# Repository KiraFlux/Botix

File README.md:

<div align="center">

# Botix

**Open‑source educational mobile robot project**

</div>

---

> **[Read this in Russian](README.ru.md)**

<br><br>

<div align="center">

## Overview

</div>

Designed for school robotics clubs, Olympiad preparation (All-Russian Olympiad, Moscow Olympiad, Russian Robotics Olympiad), and fast prototyping at hackathons. All parts are 3D‑printable, electronics are cheap and widely available.

- Two drive motors with encoders (JGA25 12V, 77-170 RPM).
- Optional [two‑degree‑of‑freedom manipulator](docs/gallery.md#2026_05_botix_esp32) (arm + gripper).
- Chassis prints in ~5 hours on a standard FDM printer; flat parts, tongue‑and‑groove assembly with screws.

<br><br>

<div align="center">

## Variants

<table>

<tr>
<td colspan="2" align="center">

**Basic**

</td>
<td colspan="2" align="center">

**Advanced**

</td>
</tr>

<tr>
<td style="padding: 0;"></td>
<td style="padding: 0;"></td>
<td style="padding: 0;"></td>
<td style="padding: 0;"></td>
</tr>

<tr valign="top">
<td colspan="2">

**For:** 
- Olympiad practice (VSOSH, MOSH, RRO), learning programming, control algorithms

**Features:**
- Arduino UNO + any motor shield
- Classic competition‑ready setup
- Simple, reliable, well‑documented

</td>
<td colspan="2">

**For:** 
- Complex algorithms, research, hackathons

**Features:**
- ESP32 as main controller (works standalone like Basic)
- Optional **[botix-esp32 firmware](botix-esp32/)** adds:
  - Remote control & telemetry via WiFi or ESP‑NOW
  - Integration with MAVLink (QGC, ROS) or custom raw protocol
  - Persistent configuration & CLI for debugging
  - LIDAR & encoder support

</td>
</tr>

<tr>
<td colspan="2" align="center">

[more_photos](docs/gallery.md#2026_07_botix_uno), 
[assembly_guide](docs/assembly_guide.md)

</td>
<td colspan="2" align="center">

[more_photos](docs/gallery.md#2026_07_botix_esp32), 
[assembly_guide](docs/assembly_guide.md), 
[firmware_docs](botix-esp32/README.md)

</td>
</tr>

</table>

</div>

> View the [printable parts catalog](docs/catalog.md).

<br><br>

<div align="center">

## Hardware

</div>

### Electronics

- **Controller** - any Developing board (Arduino UNO, ESP32, etc.). See the [assembly guide](docs/assembly_guide.md) for specific models and wiring.
- **Power board** - custom design, powered by 3×14500 cells (3S). Three independent regulators: 2 × Mini560 Pro (5V), 1 × LM2596S module (adjustable). Variants:
  - [PCB manufacturing](docs/gallery.md#2026_07_botix_power_v2_pcb_order) - production order
  - [DIY toner transfer (double-sided)](docs/gallery.md#2026_07_botix_power_v2_ttm_double)
  - [DIY toner transfer (single-sided)](docs/gallery.md#2026_07_botix_power_v2_ttm_single)

See [`ecad/README.md`](ecad/README.md).

### Mechanics

- All 3D models are in [`mcad/`](mcad/).
- [One Main assembly](mcad/botix.fcstd).
- [Chassis](mcad/chassis/) and [attachments](mcad/attachments).

See [`mcad/README.md`](mcad/README.md).

### External models

- Live in [`cadref/`](cadref/).
- Models of purchased components used as references to check fit.

See [`cadref/README.md`](cadref/README.md).

> For visual references of different robot configurations and hardware revisions, see the [project gallery](docs/gallery.md).

<br><br>

<div align="center">

## Software

<table>

<tr>
<td align="center">

**botix-esp32 firmware**

</td>
<td align="center">

**pybotix – host Python API (coming soon)**

</td>
</tr>

<tr valign="top">
<td>

The **[modular firmware](botix-esp32/)** for the Advanced variant is written in C++20 and built with PlatformIO. It provides:

- Interactive CLI for configuration and debugging
- MAVLink and RAW protocols
- ESP‑NOW and WiFi UDP transports
- Persistent configuration in NVS
- Units for motors, servos, encoders, and LIDAR

</td>
<td>

`pybotix` will be a Python package for the **host computer** (PC, Raspberry Pi). It will provide:

- Simple and safe robot control from Python
- Swarm support
- High‑level primitives for navigation and behaviors
- Eventually, block‑based code generation for education

</td>
</tr>

<tr>
<td align="center">

[firmware_docs](botix-esp32/README.md)

</td>
<td align="center">

</td>
</tr>

</table>

</div>

> `pybotix` runs on the host, not on the robot. It communicates with the robot via MAVLink or RAW protocols over WiFi/ESP‑NOW.

<br><br>

<div align="center">

## Who Is This For?

</div>

- **School students** - prepare for practical rounds of robotics Olympiads (VSOSH, MOSH, RRO). The Arduino‑based option fully matches competition regulations.
- **University students** - learn mobile robotics, navigation algorithms.
- **Hackathon participants** - the ESP32 variant with firmware provides a ready‑made infrastructure so you can focus on high‑level logic.
- **Teachers** - quickly set up robotics clubs on a low budget.

<br><br>

<div align="center">

## Quick Start

</div>

1. Read the [assembly guide](docs/assembly_guide.md).
2. Print parts from [`mcad/`](mcad/). Printable STEP files are attached to the [releases](../../releases).
3. Refer to schematics in [`ecad/`](ecad/) to assemble the electronics.
4. - For Basic: write and upload your own Arduino sketch using the motor shield library.
   - For Advanced: go to [`botix-esp32/`](botix-esp32/) and follow the firmware guide.

Before you start, make sure you have the following software installed:

| Purpose           | Software   | Version |
| ----------------- | ---------- | ------- |
| CAD (mechanics)   | FreeCAD    | 1.1.x   |
| CAD (electronics) | KiCad      | 10.x.x  |
| Slicer            | OrcaSlicer | 2.4.x   |
| Firmware build    | PlatformIO | 6.1.20  |
| Scripts runtime   | Python     | 3.14.x  |
| Render engine     | POV-Ray    | 3.7.x   |

> All tools are free and open‑source.

<br><br>

<div align="center">

## Contributing

Found a bug? Have an idea? Open an Issue or submit a Pull Request.  

</div>

> See [`CONTRIBUTING.md`](CONTRIBUTING.md) for guidelines.

<br><br>

<div align="center">

## Repository Structure & Licensing

| Path           | Description                                   |
| :------------- | :-------------------------------------------- |
| `docs/`        | Project documentation.                        |
| `cadref/`      | Reference CAD models of purchased components. |
| `mcad/`        | Project parts and assemblies in FreeCAD.      |
| `ecad/`        | PCB sources in KiCad.                         |
| `botix-esp32/` | Advanced ESP32 firmware source.               |
| `tools/`       | Automation scripts.                           |

</div>

> See [LICENSE.md](LICENSE.md) for licensing details.

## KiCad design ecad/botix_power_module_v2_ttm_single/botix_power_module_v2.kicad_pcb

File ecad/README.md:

# Electronics (KiCad)

> **[Read this in Russian](README.ru.md)**

Source files for all Botix PCBs.

## Directory Structure

| Path                                | Purpose                                           |
| ----------------------------------- | ------------------------------------------------- |
| `botix.kicad_sym`                   | Symbol library                                    |
| `botix_library.pretty/`             | Footprint library                                 |
| `botix_power_module_v2_pcb_order/`  | Manufacturing order (JLCPCB, PCBWay)              |
| `botix_power_module_v2_ttm_double/` | Double‑sided toner transfer                       |
| `botix_power_module_v2_ttm_single/` | Single‑sided toner transfer, simpler for home fab |

> The `ttm` folders are prepared for DIY toner transfer (paper + laser printer + iron).

## Editing

Open or create a file following the example of the existing ones.

A `.kicad_pro` file is the project. Schematics are `.kicad_sch`, PCB is `.kicad_pcb`.

## Export

Generated files are not stored in the repository. Export to the local artifacts directory.

## License

This README is licensed under [CC BY‑SA 4.0](../docs/LICENSE).

The hardware design files in `ecad/` are licensed under [CERN‑OHL‑S‑2.0](LICENSE).

For the complete licensing information of all project components, refer to [LICENSE.md](../LICENSE.md).

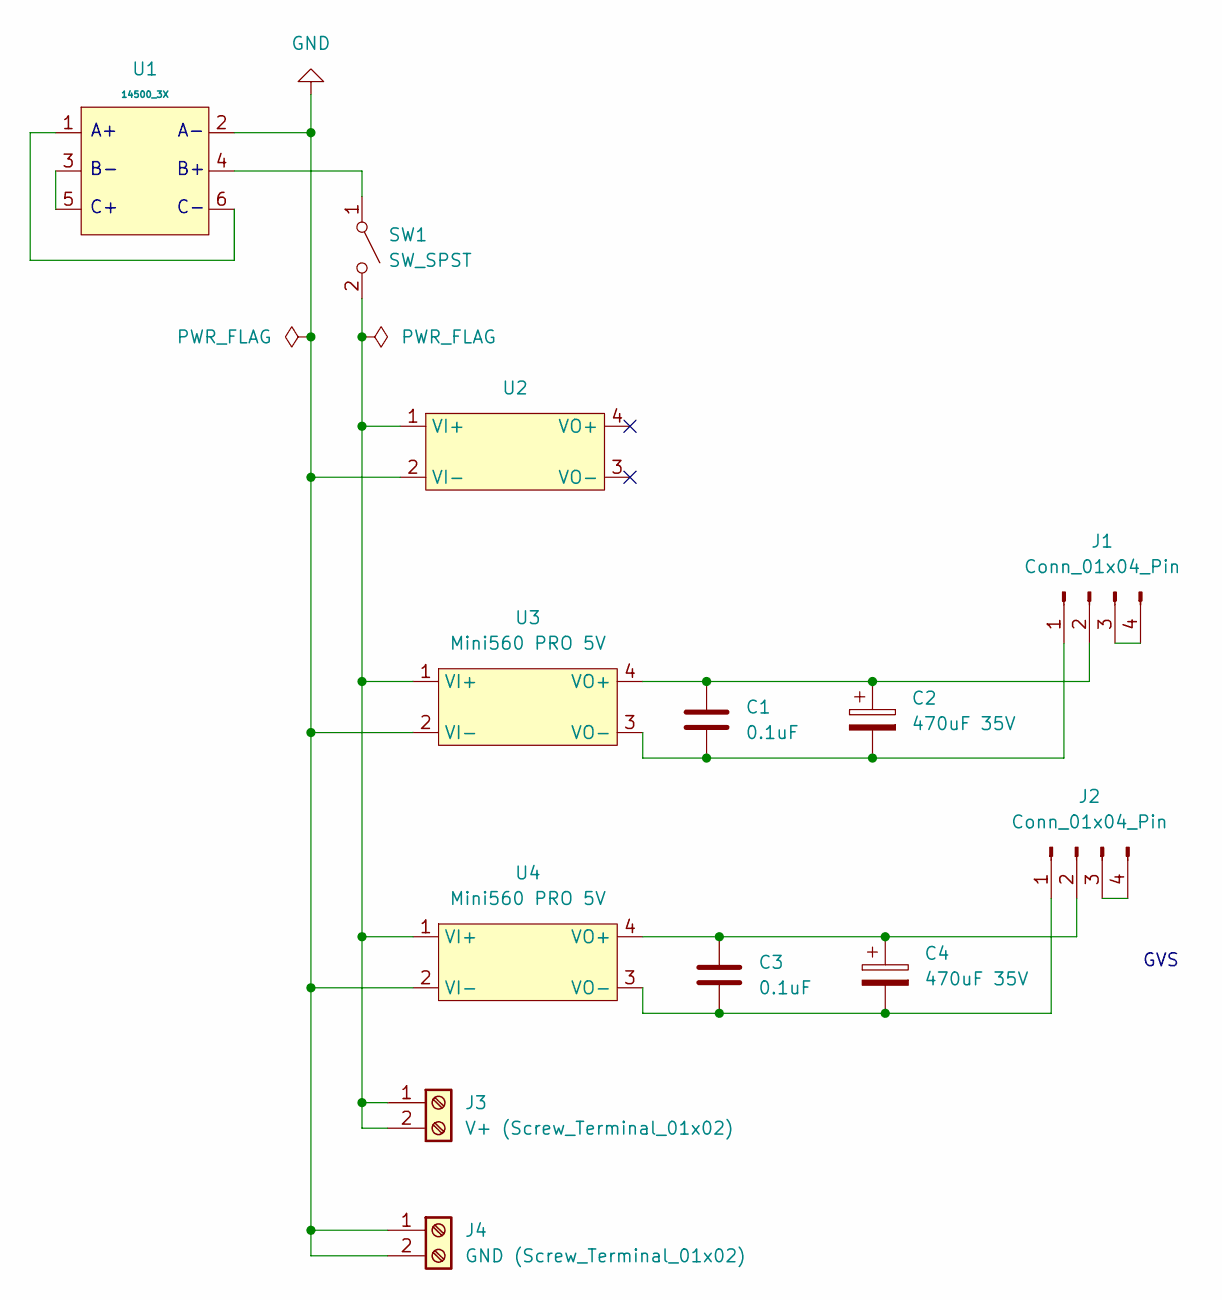
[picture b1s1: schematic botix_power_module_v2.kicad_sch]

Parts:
C1, C3: 0.1uF; C_0805_2012Metric_Pad1.18x1.45mm_HandSolder
C2, C4: 470uF 35V; C_Elec_10x10.2
J1, J2: Conn_01x04_Pin; PinHeader_1x04_P2.54mm_Horizontal
J3: V+ (Screw_Terminal_01x02); Screw_Terminal_2P_5.00mm
J4: GND (Screw_Terminal_01x02); Screw_Terminal_2P_5.00mm
SW1: SW_SPST; Switch_Rocker_KCD1-101_21x15mm
U1: 14500_3X; BatteryHolder_14500_3x_THT
U2: Converter_DCDC_LM2596S_Voltmeter
U3, U4: Mini560 PRO 5V; Converter_DCDC_Mini560Pro_33x18mm

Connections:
GND: J4.1, J4.2, U1.2, U2.2 (VI-), U3.2 (VI-), U4.2 (VI-)
unnamed: C1.2, C2.2, J1.1, U3.3 (VO-)
unnamed: C1.1, C2.1, J1.2, U3.4 (VO+)
unnamed: J1.3, J1.4
unnamed: C3.2, C4.2, J2.1, U4.3 (VO-)
unnamed: C3.1, C4.1, J2.2, U4.4 (VO+)
unnamed: J2.3, J2.4
unnamed: J3.1, J3.2, SW1.2 (B), U2.1 (VI+), U3.1 (VI+), U4.1 (VI+)
unnamed: SW1.1 (A), U1.4
unnamed: U1.1, U1.6
unnamed: U1.3, U1.5

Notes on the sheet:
GVS

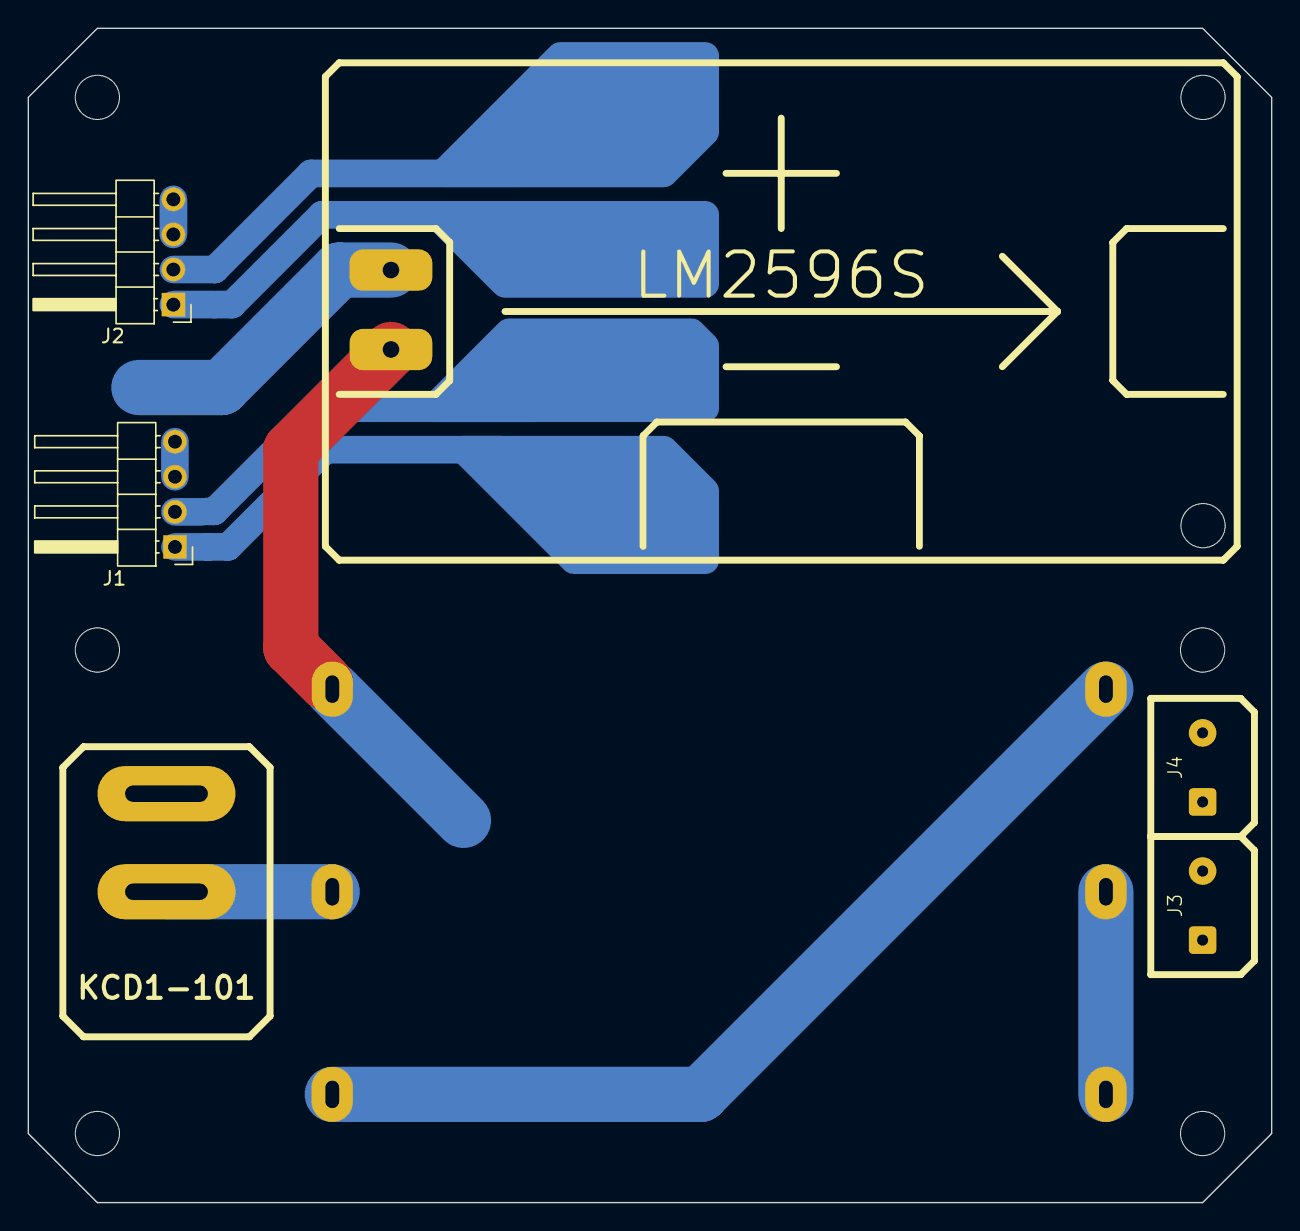
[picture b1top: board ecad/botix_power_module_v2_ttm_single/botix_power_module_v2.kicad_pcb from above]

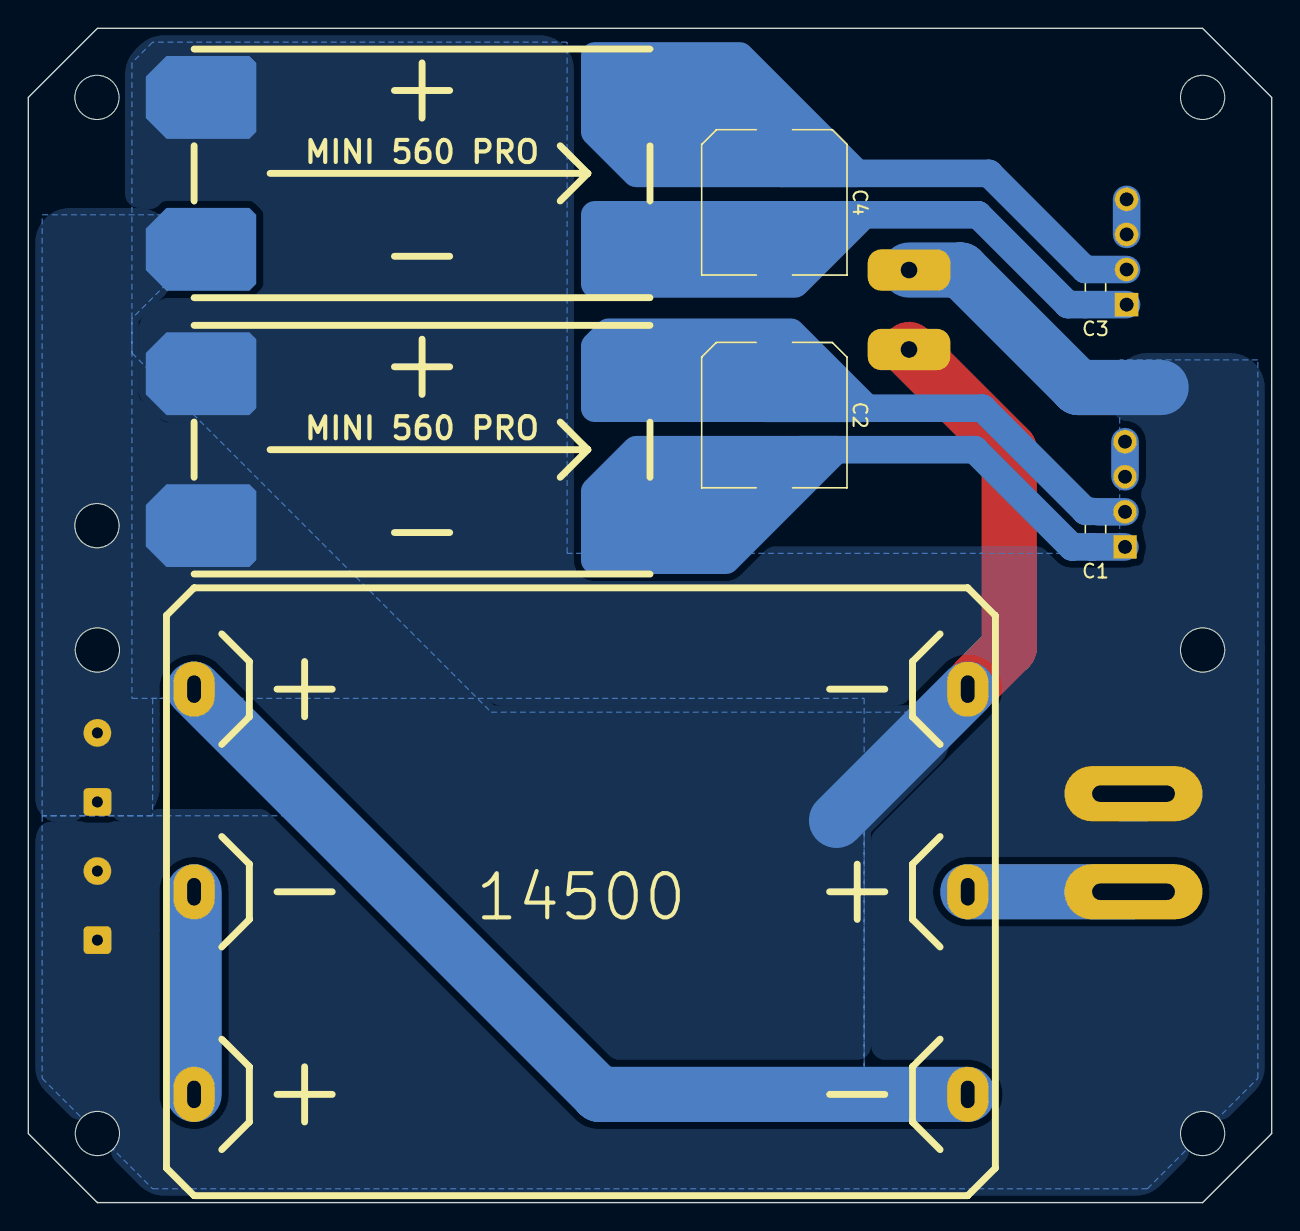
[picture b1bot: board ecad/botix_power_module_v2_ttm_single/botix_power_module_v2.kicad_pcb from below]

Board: 2 copper layers, 90.0 x 85.0 mm, 13 parts (7 on the bottom side), 11 nets.

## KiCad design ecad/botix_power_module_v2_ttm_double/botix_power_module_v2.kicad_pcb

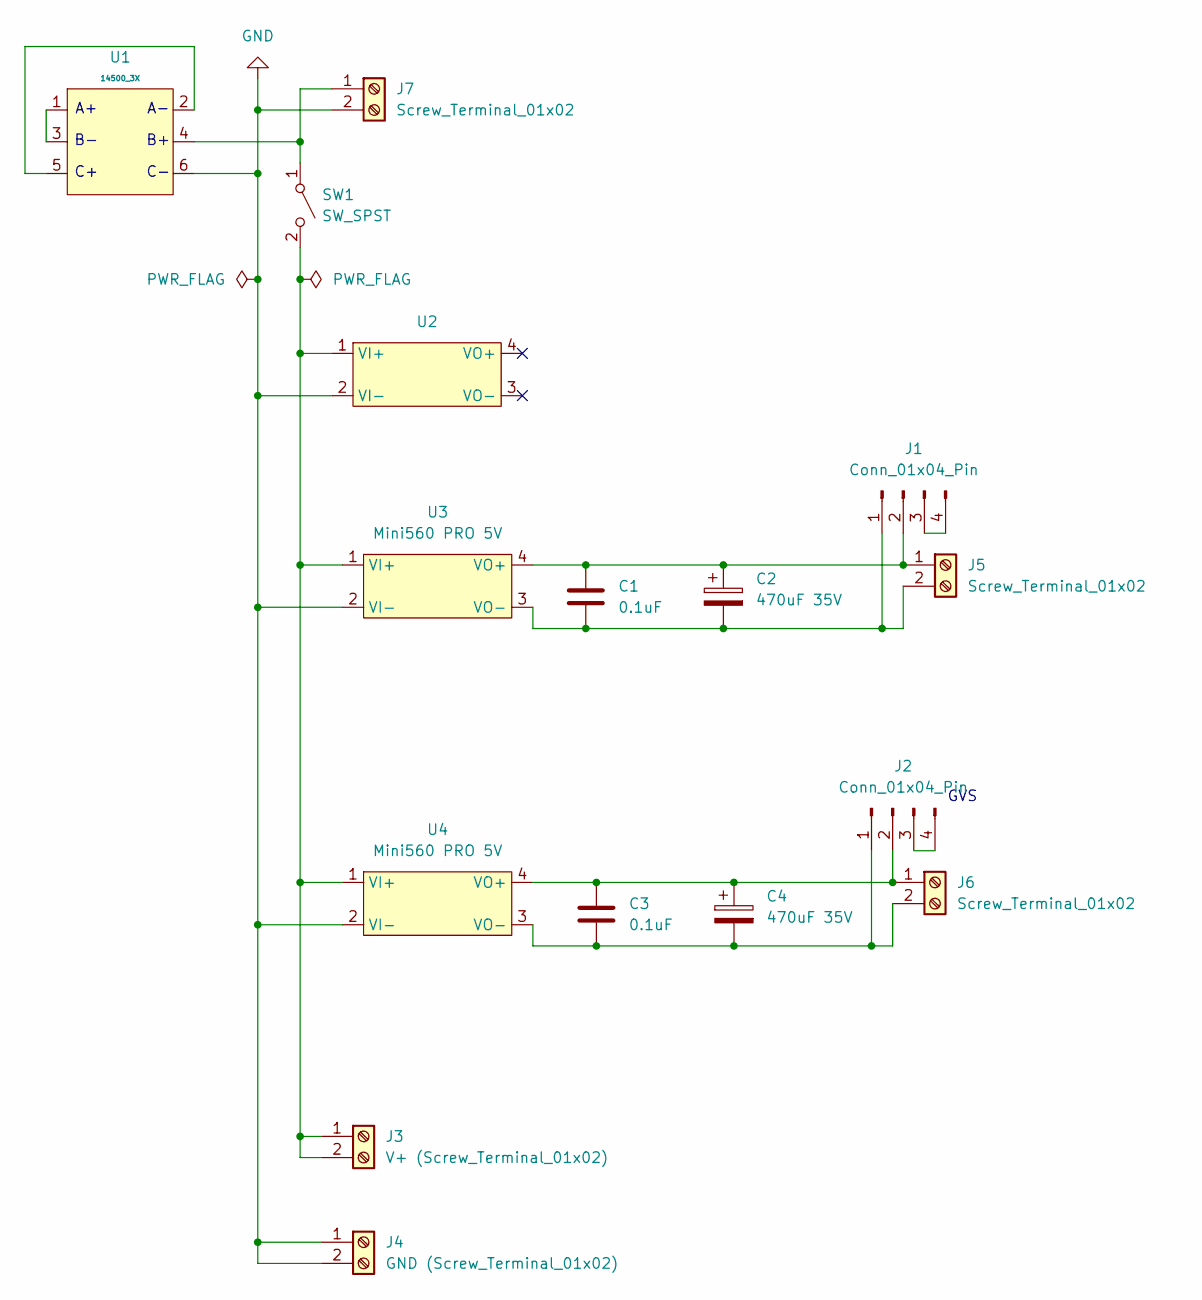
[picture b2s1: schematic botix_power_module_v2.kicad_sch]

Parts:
C1, C3: 0.1uF; C_0805_2012Metric_Pad1.18x1.45mm_HandSolder
C2, C4: 470uF 35V; CP_Radial_D10.0mm_P5.00mm
J1, J2: Conn_01x04_Pin; PinHeader_1x04_P2.54mm_Vertical
J3: V+ (Screw_Terminal_01x02); Screw_Terminal_2P_5.00mm
J4: GND (Screw_Terminal_01x02); Screw_Terminal_2P_5.00mm
J5, J6: Screw_Terminal_01x02; Screw_Terminal_KF350_2P
J7: Screw_Terminal_01x02; Screw_Terminal_2P_5.00mm
SW1: SW_SPST; Switch_Rocker_KCD1-101_21x15mm
U1: 14500_3X; BatteryHolder_14500_3x_THT
U2: Converter_DCDC_LM2596S_Voltmeter
U3, U4: Mini560 PRO 5V; Converter_DCDC_Mini560Pro_33x18mm

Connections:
GND: J4.1, J4.2, J7.2, U1.6, U2.2 (VI-), U3.2 (VI-), U4.2 (VI-)
unnamed: C1.2, C2.2, J1.1, J5.2, U3.3 (VO-)
unnamed: C1.1, C2.1, J1.2, J5.1, U3.4 (VO+)
unnamed: J1.3, J1.4
unnamed: C3.2, C4.2, J2.1, J6.2, U4.3 (VO-)
unnamed: C3.1, C4.1, J2.2, J6.1, U4.4 (VO+)
unnamed: J2.3, J2.4
unnamed: J3.1, J3.2, SW1.2 (B), U2.1 (VI+), U3.1 (VI+), U4.1 (VI+)
unnamed: J7.1, SW1.1 (A), U1.4
unnamed: U1.1, U1.3
unnamed: U1.2, U1.5

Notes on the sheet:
GVS

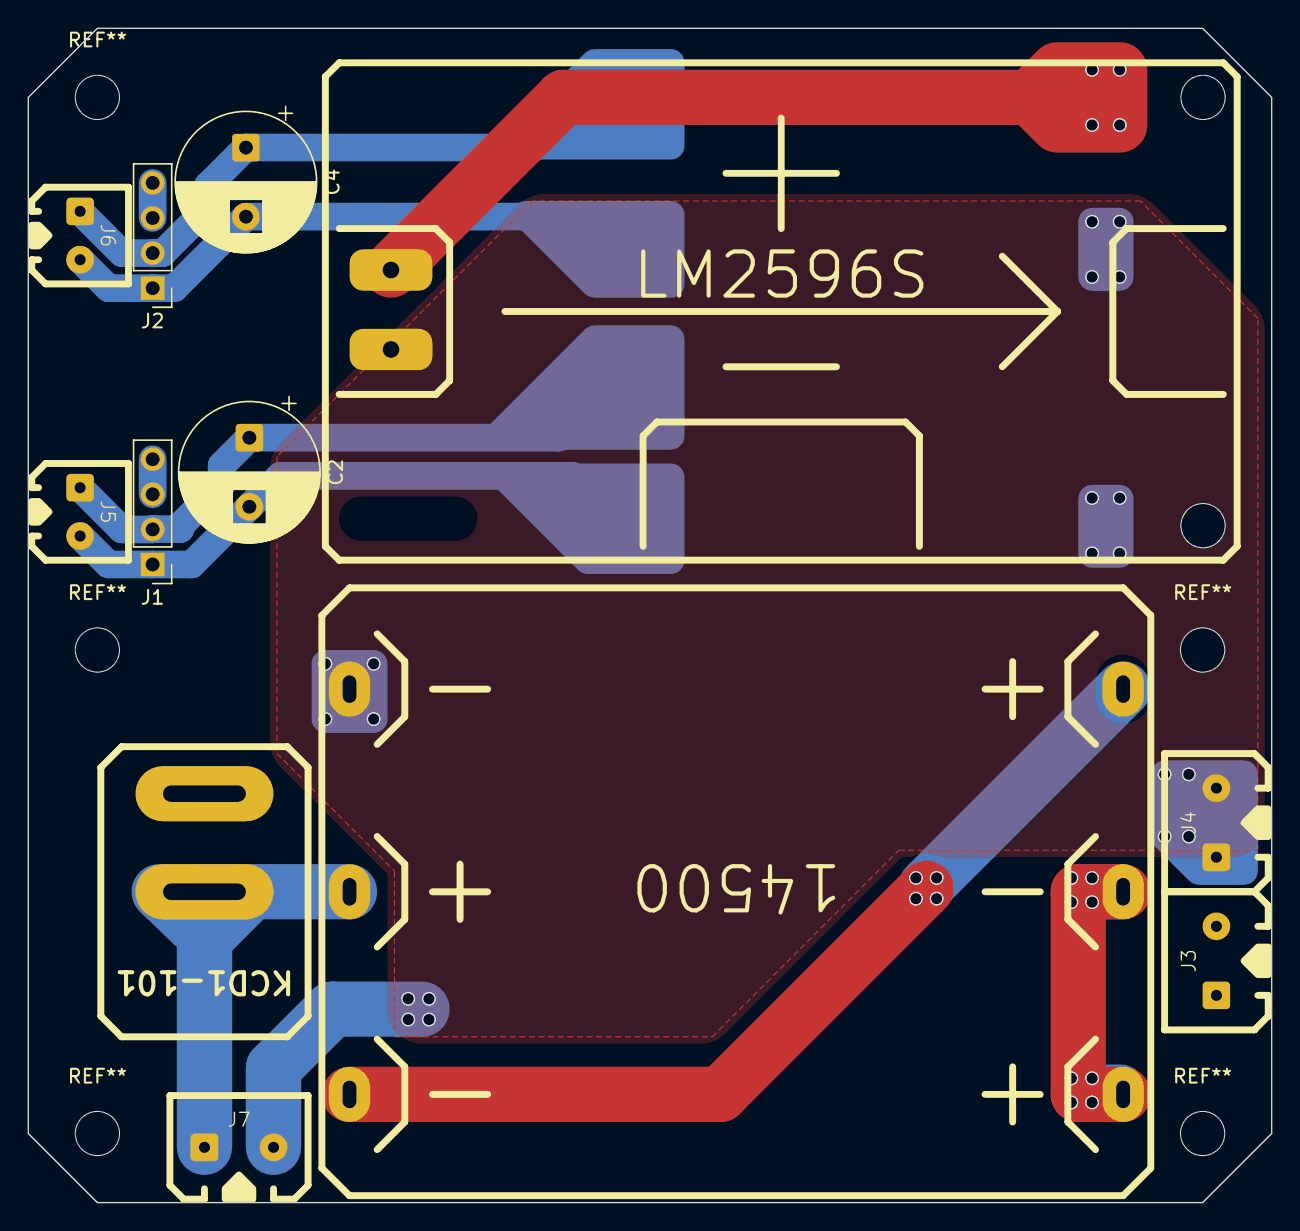
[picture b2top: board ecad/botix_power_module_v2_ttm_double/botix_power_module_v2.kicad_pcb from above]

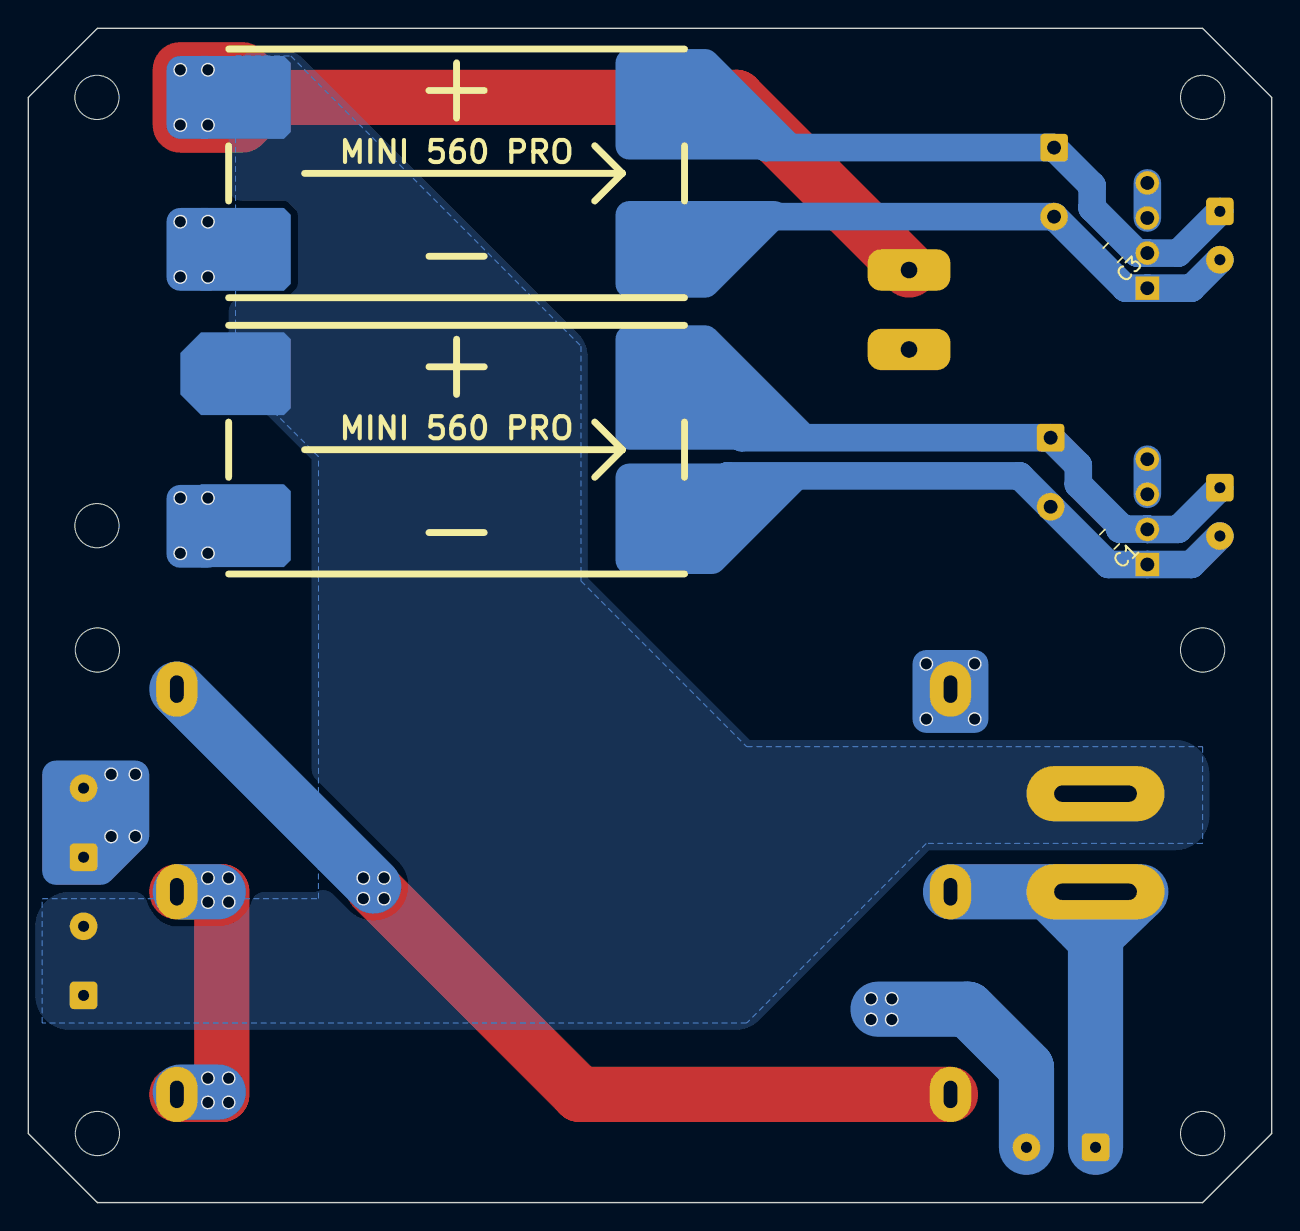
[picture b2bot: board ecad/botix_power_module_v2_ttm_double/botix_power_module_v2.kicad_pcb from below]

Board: 2 copper layers, 90.0 x 85.0 mm, 16 parts (4 on the bottom side), 11 nets.

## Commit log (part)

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2024-12-02 init
2024-12-08 Add README.md
2024-12-08 Добавлен каталог "Код"
2024-12-08 Добавлен Модуль сервопривода Signed-off-by: JamahaW <153020210+JamahaW@users.noreply.github.com>
2024-12-10 Добавлены .STP модели для печать Обновлена платформа MIDI-Q
2024-12-11 Обновлена модель midi-q_v611__v611.stp v6.3
2024-12-11 Обновлен скрипт очистки
2024-12-11 Фикс платформа v6.3 Починка модели STEP
2024-12-11 Обновлен Gcode
2024-12-11 Добавлен проект Prusa платформы midi-q_v63.3mf
2024-12-11 v611.m3d -> Платформа.m3d
2024-12-12 Обновлена сборка MIDI-Q Шасси
2024-12-12 Добавлен аналог колеса D67 под 3D-печать
2024-12-12 Обновлен скрипт
2024-12-15 Обновлен
2025-05-08 mass refactor
2025-05-27 Рефакторинг папки моделей. 1) TODO: Доделать: Модели\Профили\Устаревшие 2) FIXME: СЛОМАНЫ СВЯЗИ И ПУТИ.
2025-05-28 upd README.md
2025-06-04 part builder
2025-06-04 unit load
2025-06-04 section load
2025-06-05 iterDirs fix
2025-06-05 SectionLoader fix
2025-06-05 Колеса -> Колесо
2025-06-05 section attributes
2025-06-05 add .section files to sections folders
2025-06-05 rem CleanupConfig.json
2025-06-05 project entity loading
2025-06-05 text render
2025-06-05 unit tr
2025-06-05 section tr
2025-06-05 project tr
2025-06-11 refactor
2025-06-11 refactor loaders
2025-06-11 refactor loaders impl
2025-06-11 refactor loaders impl + visitor
2025-06-13 upd text engine
2025-06-14 upd issue
2025-08-15 upd gitignore
2025-09-10 Добавлен архив файлов для производства MidiQ-Всош-v2--2025.09.10.zip
2025-09-10 Добавлен README.md с обзором сборок для производства
2025-09-13 Тест Авторелиз
2025-09-13 Тест Авторелиз 2
2025-09-19 Исправлены .stp файлы экспорта деталей шасси MidiQ-Всош-v2
2025-09-19 Добавлен .unit для экспорта Шасси MidiQ-Всош-v2
2025-09-20 Исправление метаданных сборки MidiQ-Всош-v2
2025-09-20 Экспорт сборки MidiQ-Всош-v2 в step 203
2025-09-20 #20 Исправление наименования MidiQ/Стенка-Задняя
2025-09-20 Уточнения в docstring
2025-09-20 переименование пакета projectmaster -> botix
2025-09-20 fix #21
2025-09-20 fix #22
2025-09-20 Добавлена PartsSectionEntity - Поиск среди общих деталей
2025-09-20 fix #23 Настройка выпуска сборки .unit теперь позволяет искать глобальные детали
2025-09-20 Автоматическое создание выпусков для производства
2025-09-20 Обновлён README.md
2025-09-20 Исправлена кодировка
2025-09-20 фиксы
